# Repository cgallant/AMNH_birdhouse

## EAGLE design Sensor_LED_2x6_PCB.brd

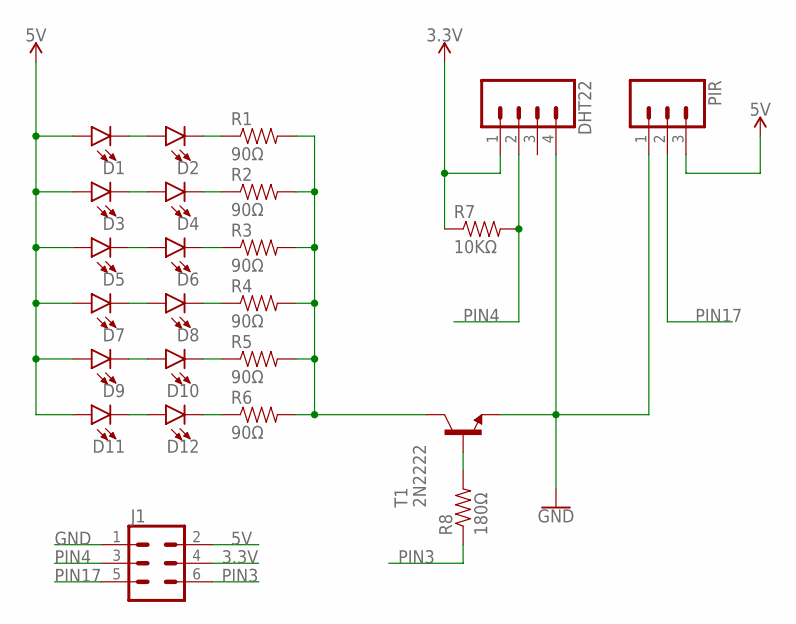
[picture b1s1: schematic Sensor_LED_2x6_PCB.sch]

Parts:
D1, D2, D3, D4, D5, D6, D7, D8, D9, D10, D11, D12: LED5MM; LED_5MM
DHT22: CONN_04LONGPADS; 1X04_LONGPADS
J1: CONN_03X2SHROUD; 2X3-SHROUDED
PIR: CONN_03LONGPADS; 1X03_LONGPADS
R1, R2, R3, R4, R5, R6: 90Ω; 1206
R7: 10KΩ; 1206
R8: 180Ω; 1206
T1: 2N2222; TO92-EBC-OVAL

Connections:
3.3V: DHT22.1, J1.4, R7.1
5V: D1.A, D3.A, D5.A, D7.A, D9.A, D11.A, J1.2, PIR.3
GND: DHT22.4, J1.1, PIR.1, T1.E
unnamed: D1.K (C), D2.A
unnamed: D3.K (C), D4.A
unnamed: D5.K (C), D6.A
unnamed: R8.2, T1.B
unnamed: D7.K (C), D8.A
unnamed: D12.K (C), R6.1
unnamed: R1.2, R2.2, R3.2, R4.2, R5.2, R6.2, T1.C
unnamed: D2.K (C), R1.1
unnamed: D9.K (C), D10.A
unnamed: D4.K (C), R2.1
unnamed: D6.K (C), R3.1
unnamed: D8.K (C), R4.1
unnamed: D10.K (C), R5.1
unnamed: D11.K (C), D12.A
PIN3: J1.6, R8.1
PIN4: DHT22.2, J1.3, R7.2
PIN17: J1.5, PIR.2

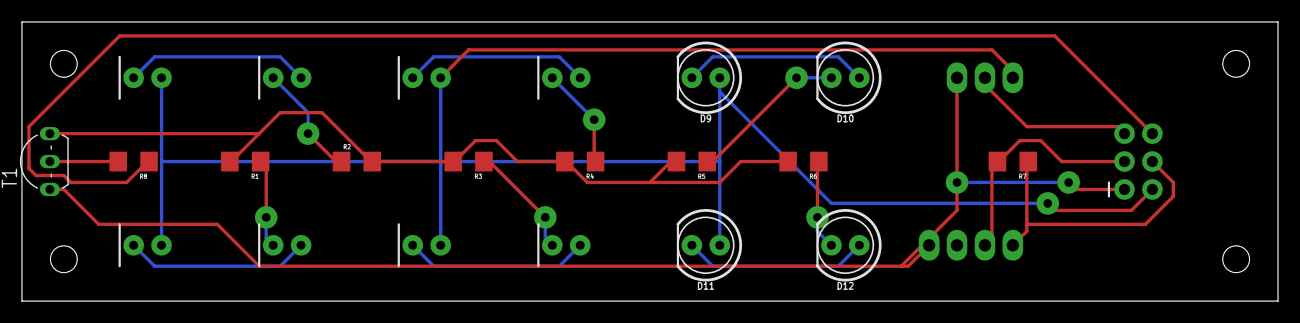
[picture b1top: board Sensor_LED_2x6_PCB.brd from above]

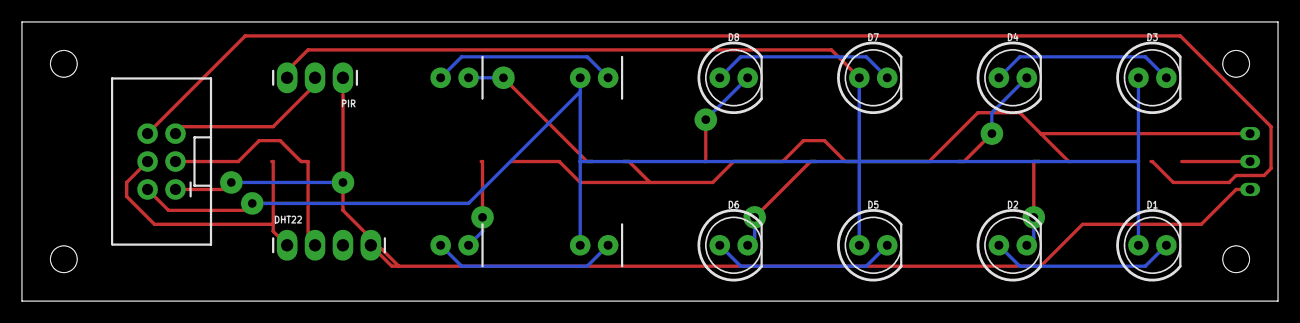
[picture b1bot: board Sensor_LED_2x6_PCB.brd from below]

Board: 2 copper layers, 114.3 x 25.4 mm, 24 parts (11 on the bottom side), 20 nets.

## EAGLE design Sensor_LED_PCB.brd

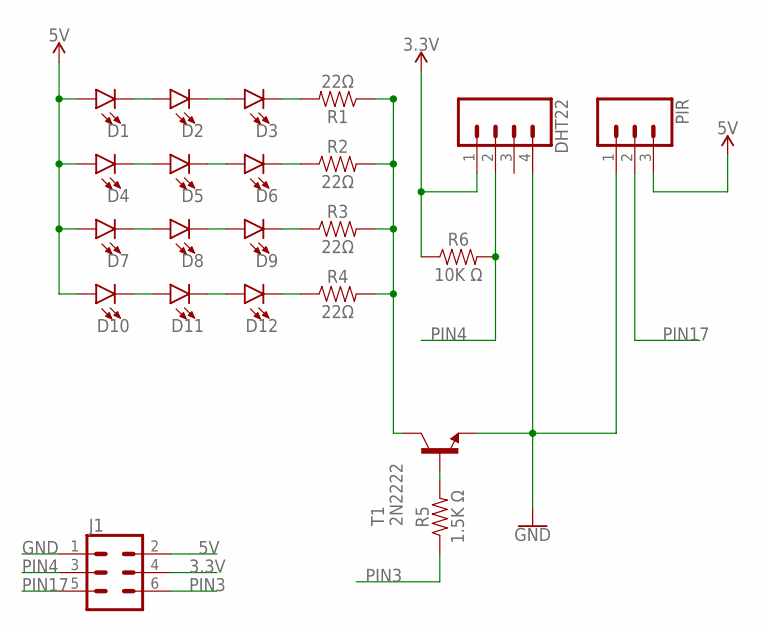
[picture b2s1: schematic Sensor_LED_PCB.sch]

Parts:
D1, D2, D3, D4, D5, D6, D7, D8, D9, D10, D11, D12: LED5MM; LED_5MM
DHT22: CONN_04LONGPADS; 1X04_LONGPADS
J1: CONN_03X2SHROUD; 2X3-SHROUDED
PIR: CONN_03LONGPADS; 1X03_LONGPADS
R1, R2, R3, R4: 22Ω; AXIAL-0.3-KIT
R5: 1.5K Ω; AXIAL-0.3-KIT
R6: 10K Ω; AXIAL-0.3-KIT
T1: 2N2222; TO92-EBC-OVAL

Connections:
3.3V: DHT22.1, J1.4, R6.P$1 (1)
5V: D1.A, D4.A, D7.A, D10.A, J1.2, PIR.3
GND: DHT22.4, J1.1, PIR.1, T1.E
unnamed: D1.K (C), D2.A
unnamed: D4.K (C), D5.A
unnamed: D7.K (C), D8.A
unnamed: R5.P$2 (2), T1.B
unnamed: D10.K (C), D11.A
unnamed: R1.P$1 (1), R2.P$2 (2), R3.P$2 (2), R4.P$2 (2), T1.C
unnamed: D2.K (C), D3.A
unnamed: D3.K (C), R1.P$2 (2)
unnamed: D5.K (C), D6.A
unnamed: D8.K (C), D9.A
unnamed: D11.K (C), D12.A
unnamed: D6.K (C), R2.P$1 (1)
unnamed: D9.K (C), R3.P$1 (1)
unnamed: D12.K (C), R4.P$1 (1)
PIN3: J1.6, R5.P$1 (1)
PIN4: DHT22.2, J1.3, R6.P$2 (2)
PIN17: J1.5, PIR.2

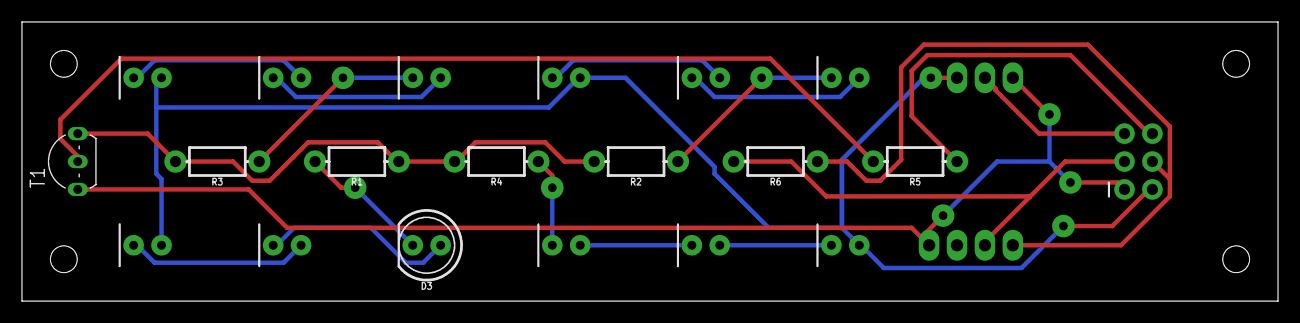
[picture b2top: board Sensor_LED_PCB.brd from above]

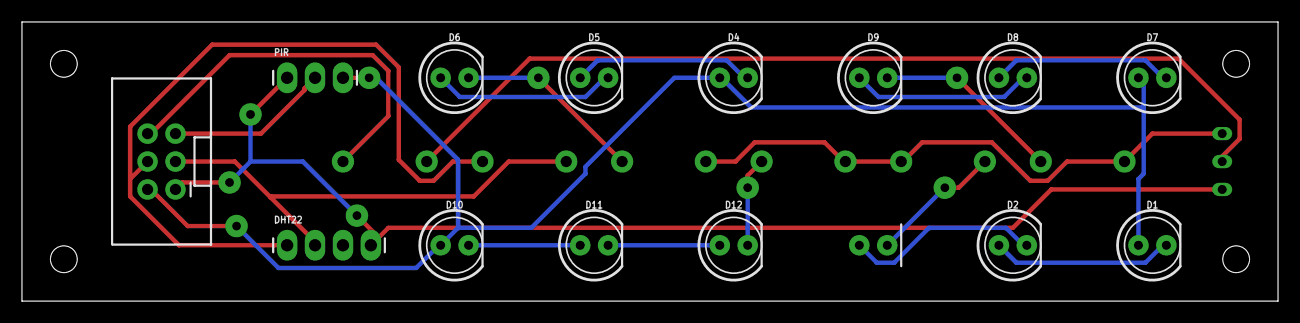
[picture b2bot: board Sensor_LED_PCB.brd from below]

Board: 2 copper layers, 114.3 x 25.4 mm, 22 parts (14 on the bottom side), 20 nets.

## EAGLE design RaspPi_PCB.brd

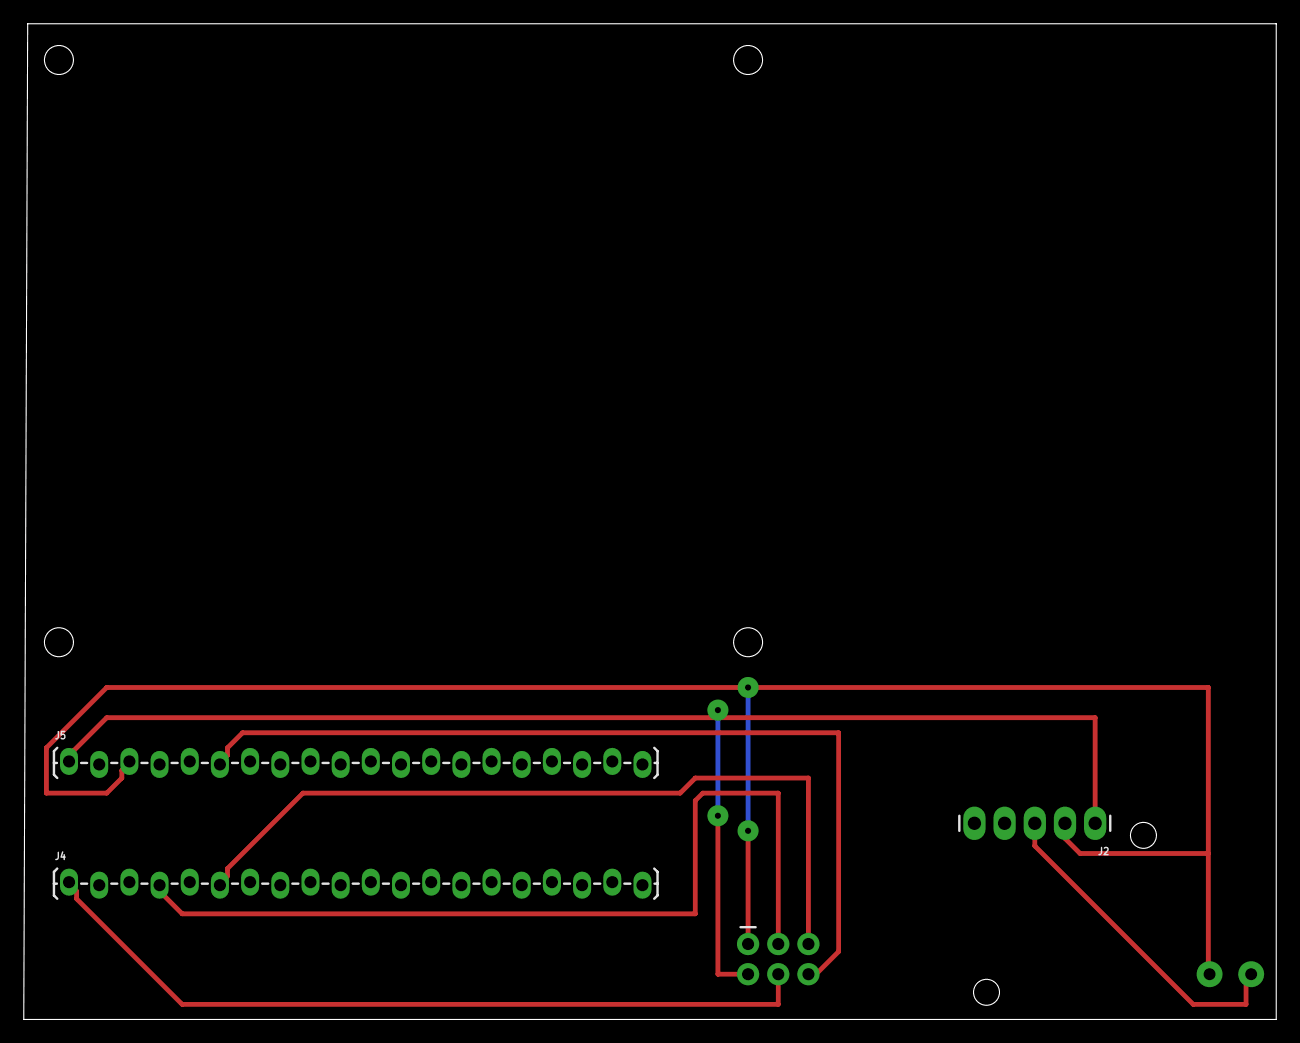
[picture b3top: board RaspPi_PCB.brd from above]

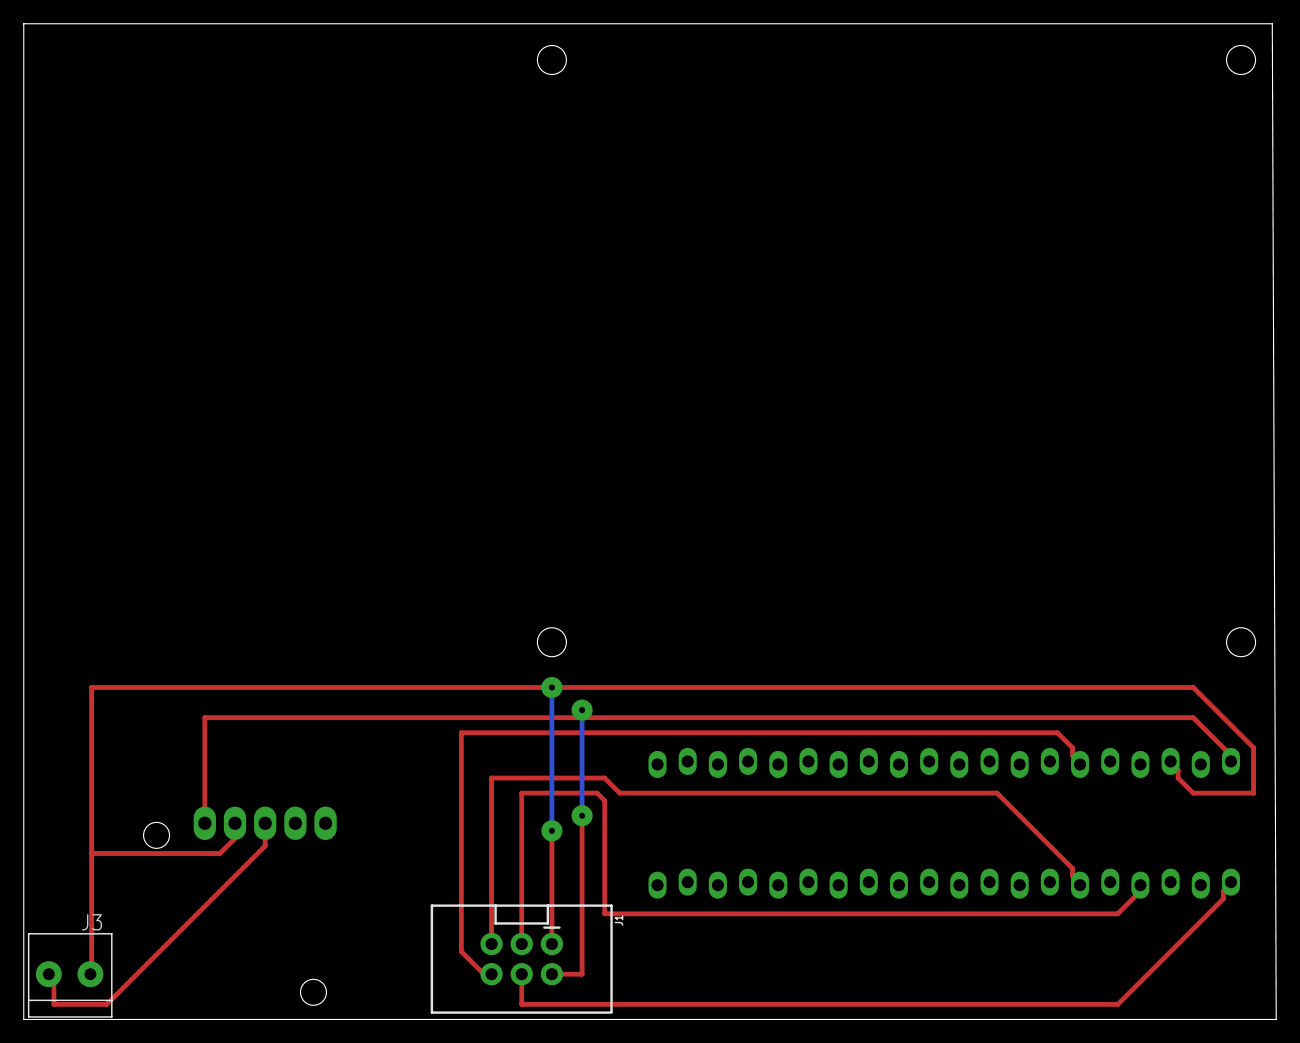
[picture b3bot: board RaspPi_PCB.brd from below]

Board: 2 copper layers, 105.4 x 83.8 mm, 5 parts (2 on the bottom side), 7 nets.

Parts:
J1: 2X3-SHROUDED
J2: 1X05_LONGPADS
J3: 1X2-3.5MM
J4, J5: 1X20_LOCK_LONGPADS

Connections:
3.3V: J1.4, J4.1
5V: J1.2, J2.1, J5.1
GND: J1.1, J2.2, J3.1, J5.3
PIN4: J1.3, J4.4
PIN17: J1.5, J4.6
PIN18: J1.6, J5.6
VIN: J2.3, J3.2

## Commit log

2017-12-06 change size of board to fit Bantam Tools alignment bracket
2017-12-06 Change names of files to decribe what the PCB is, since there will be two PCBs
2017-12-06 Change DRC to 1/64
2017-12-06 Put LED resistors in series, not parallel.
2017-12-06 Redo: Put LED resistors in series, not parallel.
2017-12-07 Rename files and create RaspPi files
2017-12-07 Add and initial commit for main pcb.
2017-12-07 Change RaspPi board to switch the side that the Pi is on and to switch the two Pi headers.
2017-12-07 Rotate main pcb so it can be printed on the other mill.
2017-12-07 Flip voltage regulator
2017-12-08 Changes localley
2017-12-09 changed to six sets of series

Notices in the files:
parts and their libraries:
SparkFun-Connectors: Licensing: Creative Commons ShareAlike 4.0 International - https://creativecommons.org/licenses/by-sa/4.0
